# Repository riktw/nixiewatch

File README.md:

# Nixie (ok, panaplex) watch
hardware and software for a panaplex watch.

More info can be found on the corresponding [blog post.](https://justanotherelectronicsblog.com/?p=1190)

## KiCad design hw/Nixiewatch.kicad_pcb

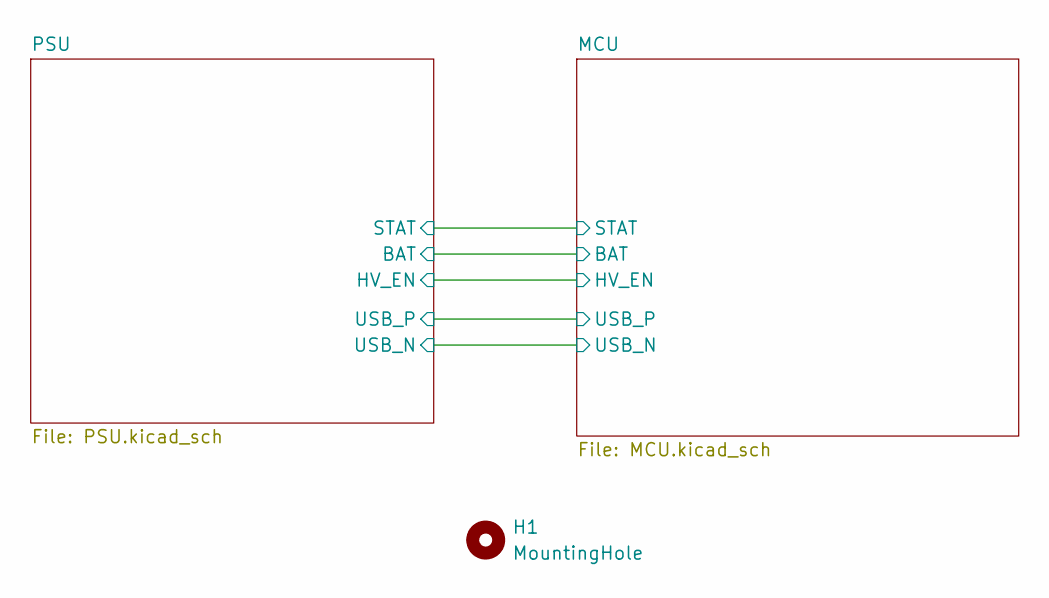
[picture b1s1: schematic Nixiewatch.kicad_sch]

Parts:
H1: MountingHole; MountingHole_2.2mm_M2

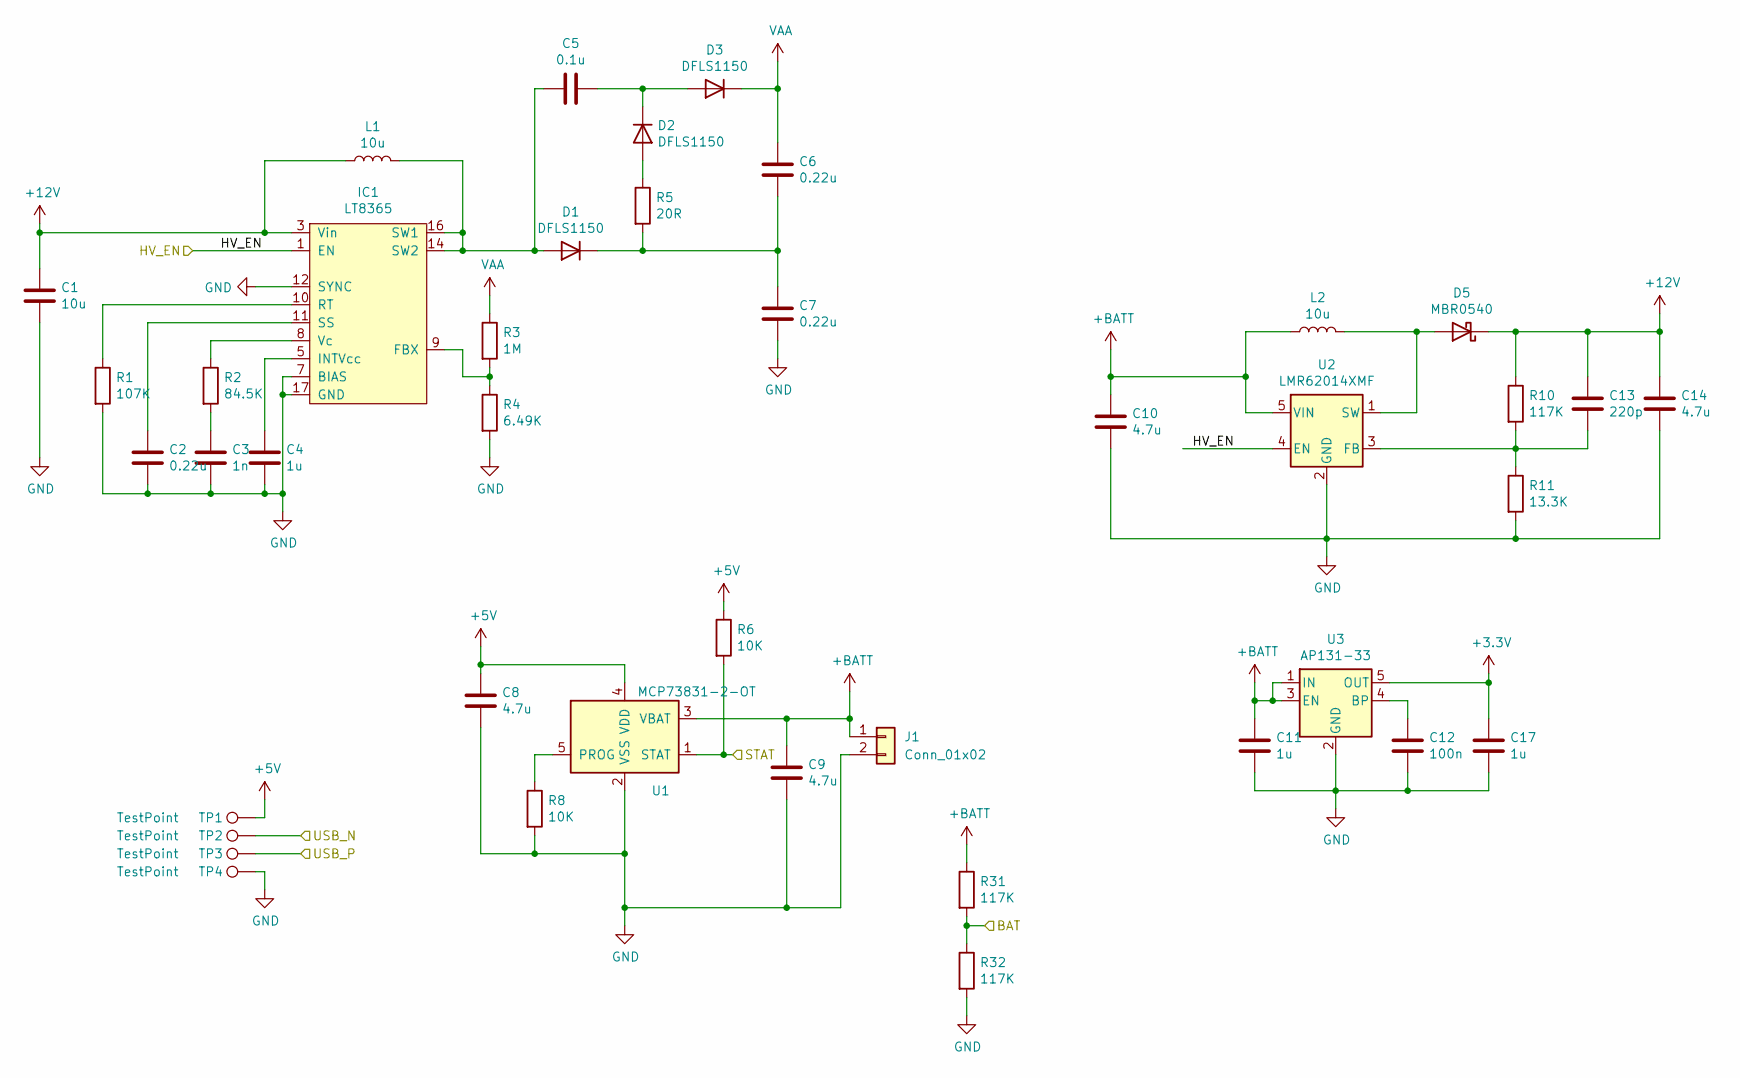
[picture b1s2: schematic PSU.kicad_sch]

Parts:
C1: 10u; C_0805_2012Metric_Pad1.15x1.40mm_HandSolder
C2: 0.22u; C_0603_1608Metric
C3: 1n; C_0603_1608Metric
C4, C11, C17: 1u; C_0603_1608Metric
C5: 0.1u; C_1206_3216Metric
C6, C7: 0.22u; C_1206_3216Metric
C8, C9, C10, C14: 4.7u; C_0603_1608Metric
C12: 100n; C_0603_1608Metric; LCSC C14663
C13: 220p; C_0603_1608Metric
D1, D2, D3: DFLS1150; D_SOD-123
D5: MBR0540; D_SOD-123
IC1: LT8365; MSOP-16-3x4.039_HV
J1: Conn_01x02; PinHeader_1x02_P2.54mm_Vertical
L1, L2: 10u; L_Coilcraft_XxL4020
R1: 107K; R_0603_1608Metric
R2: 84.5K; R_0603_1608Metric
R3: 1M; R_1206_3216Metric
R4: 6.49K; R_0603_1608Metric
R5: 20R; R_0603_1608Metric
R6, R8: 10K; R_0603_1608Metric
R10, R31, R32: 117K; R_0603_1608Metric
R11: 13.3K; R_0603_1608Metric
TP1, TP2, TP3, TP4: TestPoint; TestPoint_Pad_D1.5mm
U1: MCP73831-2-OT; SOT-23-5
U2: LMR62014XMF; SOT-23-5
U3: AP131-33; SOT-23-5

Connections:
+3V3: C17.1, U3.5 (OUT); also elsewhere on the board
+5V: C8.1, R6.1, TP1.1, U1.4 (VDD)
+12V: C1.1, C13.1, C14.1, D5.1 (K), IC1.3 (Vin), L1.1, R10.1
+BATT: C9.1, C10.1, C11.1, J1.1, L2.1, R31.1, U1.3 (VBAT), U2.5 (VIN), U3.1 (IN), U3.3 (EN)
/MCU/BAT: R31.2, R32.1; also elsewhere on the board
/MCU/STAT: R6.2, U1.1 (STAT); also elsewhere on the board
/MCU/USB_N: TP2.1; also elsewhere on the board
/MCU/USB_P: TP3.1; also elsewhere on the board
/PSU/HV_EN: IC1.1 (EN), U2.4 (EN); also elsewhere on the board
GND: C1.2, C2.2, C3.2, C4.2, C7.2, C8.2, C9.2, C10.2, C11.2, C12.2, C14.2, C17.2, IC1.7 (BIAS), IC1.12 (SYNC), IC1.17 (GND), J1.2, R1.2, R4.2, R8.2, R11.2, R32.2, TP4.1, U1.2 (VSS), U2.2 (GND), U3.2 (GND); also elsewhere on the board
unnamed: C2.1, IC1.11 (SS)
unnamed: C3.1, R2.2
unnamed: C4.1, IC1.5 (INTVcc)
unnamed: C5.1, D1.2 (A), IC1.14 (SW2), IC1.16 (SW1), L1.2
unnamed: C5.2, D2.1 (K), D3.2 (A)
unnamed: C6.2, C7.1, D1.1 (K), R5.2
unnamed: C12.1, U3.4 (BP)
unnamed: C13.2, R10.2, R11.1, U2.3 (FB)
unnamed: D2.2 (A), R5.1
unnamed: D5.2 (A), L2.2, U2.1 (SW)
unnamed: IC1.8 (Vc), R2.1
unnamed: IC1.9 (FBX), R3.2, R4.1
unnamed: IC1.10 (RT), R1.1
unnamed: R8.1, U1.5 (PROG)
VAA: C6.1, D3.1 (K), R3.1; also elsewhere on the board

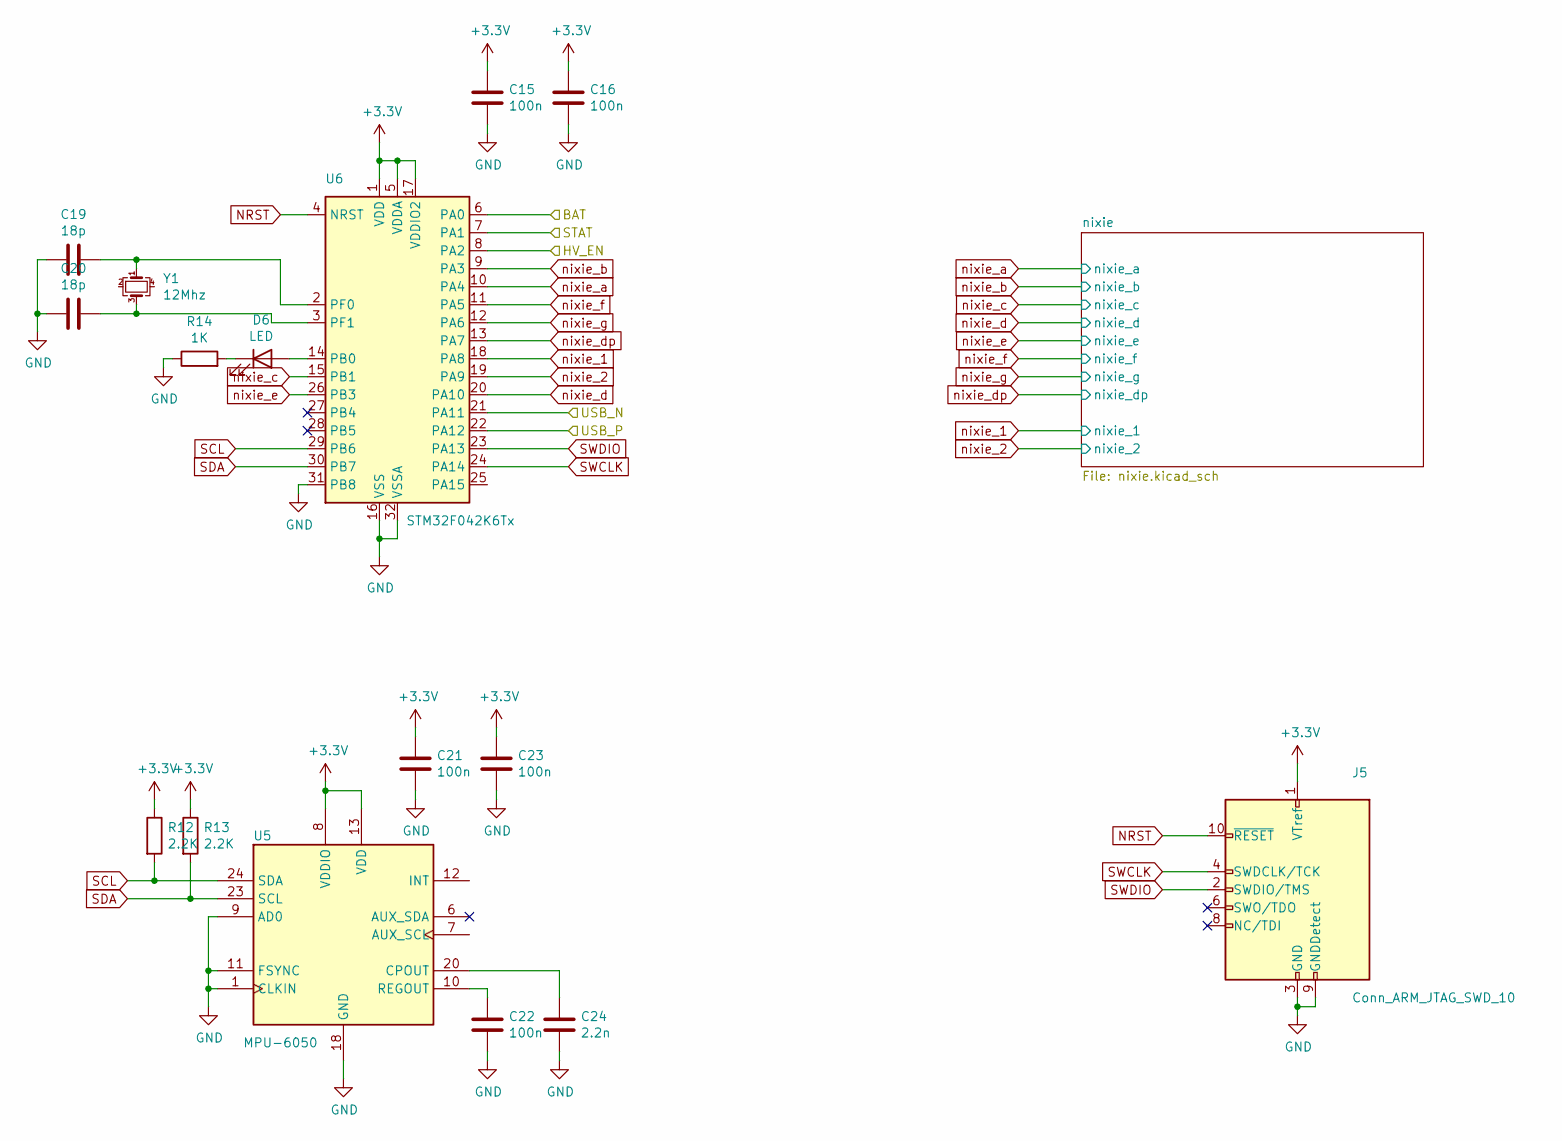
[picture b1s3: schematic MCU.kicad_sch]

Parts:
C15, C16, C21, C22, C23: 100n; C_0603_1608Metric; LCSC C14663
C19, C20: 18p; C_0603_1608Metric
C24: 2.2n; C_0603_1608Metric
D6: LED; LED_0603_1608Metric_Pad1.05x0.95mm_HandSolder
J5: Conn_ARM_JTAG_SWD_10; PinHeader_2x05_P1.27mm_Vertical_SMD
R12, R13: 2.2K; R_0603_1608Metric
R14: 1K; R_0603_1608Metric
U5: MPU-6050; InvenSense_QFN-24_4x4mm_P0.5mm
U6: STM32F042K6Tx; LQFP-32_7x7mm_P0.8mm
Y1: 12Mhz; Crystal_SMD_3225-4Pin_3.2x2.5mm_HandSoldering

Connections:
+3V3: C15.1, C16.1, C21.1, C23.1, J5.1 (VTref), R12.1, R13.1, U5.8 (VDDIO), U5.13 (VDD), U6.1 (VDD), U6.5 (VDDA), U6.17 (VDDIO2); also elsewhere on the board
/MCU/BAT: U6.6 (PA0); also elsewhere on the board
/MCU/STAT: U6.7 (PA1); also elsewhere on the board
/MCU/USB_N: U6.21 (PA11); also elsewhere on the board
/MCU/USB_P: U6.22 (PA12); also elsewhere on the board
/PSU/HV_EN: U6.8 (PA2); also elsewhere on the board
GND: C15.2, C16.2, C19.2, C20.2, C21.2, C22.2, C23.2, C24.2, J5.3 (GND), J5.5 (GND), J5.9 (GNDDetect), R14.1, U5.1 (CLKIN), U5.9 (AD0), U5.11 (FSYNC), U5.18 (GND), U6.16 (VSS), U6.31 (PB8), U6.32 (VSSA); also elsewhere on the board
NRST: J5.10 (~RESET), U6.4 (NRST)
unnamed: C19.1, U6.2 (PF0), Y1.1
unnamed: C20.1, U6.3 (PF1), Y1.3
unnamed: C22.1, U5.10 (REGOUT)
unnamed: C24.1, U5.20 (CPOUT)
unnamed: D6.1 (K), R14.2
unnamed: D6.2 (A), U6.14 (PB0)
SCL: R12.2, U5.24 (SDA), U6.29 (PB6)
SDA: R13.2, U5.23 (SCL), U6.30 (PB7)
SWCLK: J5.4 (SWDCLK/TCK), U6.24 (PA14)
SWDIO: J5.2 (SWDIO/TMS), U6.23 (PA13)
nixie_1: U6.18 (PA8); also elsewhere on the board
nixie_2: U6.19 (PA9); also elsewhere on the board
nixie_a: U6.10 (PA4); also elsewhere on the board
nixie_b: U6.9 (PA3); also elsewhere on the board
nixie_c: U6.15 (PB1); also elsewhere on the board
nixie_d: U6.20 (PA10); also elsewhere on the board
nixie_dp: U6.13 (PA7); also elsewhere on the board
nixie_e: U6.26 (PB3); also elsewhere on the board
nixie_f: U6.11 (PA5); also elsewhere on the board
nixie_g: U6.12 (PA6); also elsewhere on the board

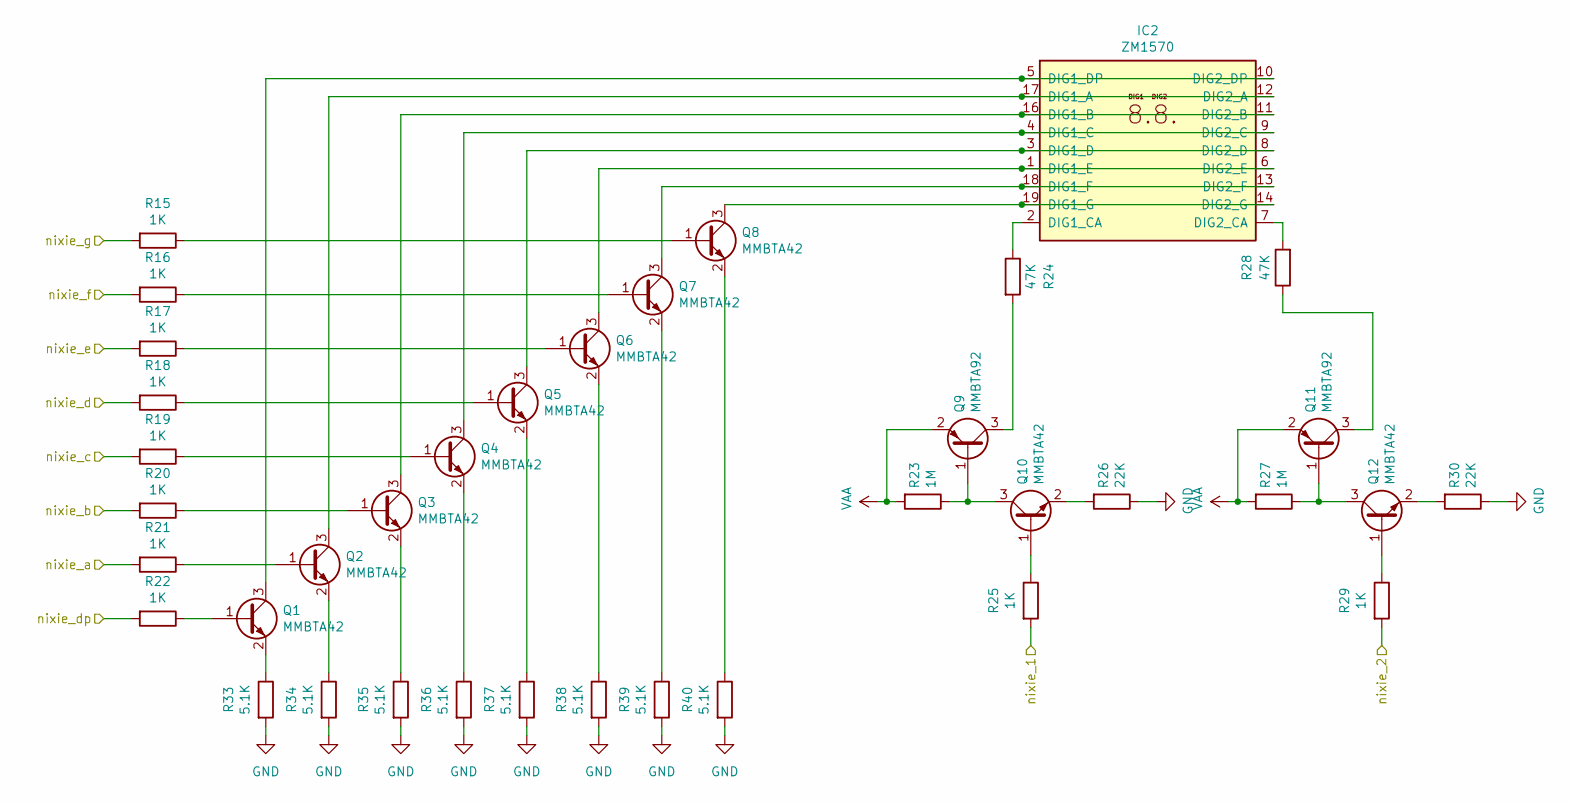
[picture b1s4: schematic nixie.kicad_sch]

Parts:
IC2: ZM1570
Q1, Q2, Q3, Q4, Q5, Q6, Q7, Q8, Q10, Q12: MMBTA42; SOT-23
Q9, Q11: MMBTA92; SOT-23
R15, R16, R17, R18, R19, R20, R21, R22, R25, R29: 1K; R_0603_1608Metric
R23, R27: 1M; R_0603_1608Metric
R24, R28: 47K; R_0805_2012Metric_Pad1.15x1.40mm_HandSolder
R26, R30: 22K; R_0603_1608Metric
R33, R34, R35, R36, R37, R38, R39, R40: 5.1K; R_0603_1608Metric

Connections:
GND: R26.1, R30.1, R33.2, R34.2, R35.2, R36.2, R37.2, R38.2, R39.2, R40.2; also elsewhere on the board
unnamed: IC2.1 (DIG1_E), IC2.6 (DIG2_E), Q6.3 (C)
unnamed: IC2.2 (DIG1_CA), R24.1
unnamed: IC2.3 (DIG1_D), IC2.8 (DIG2_D), Q5.3 (C)
unnamed: IC2.4 (DIG1_C), IC2.9 (DIG2_C), Q4.3 (C)
unnamed: IC2.7 (DIG2_CA), R28.2
unnamed: IC2.5 (DIG1_DP), IC2.10 (DIG2_DP), Q1.3 (C)
unnamed: IC2.11 (DIG2_B), IC2.16 (DIG1_B), Q3.3 (C)
unnamed: IC2.12 (DIG2_A), IC2.17 (DIG1_A), Q2.3 (C)
unnamed: IC2.13 (DIG2_F), IC2.18 (DIG1_F), Q7.3 (C)
unnamed: IC2.14 (DIG2_G), IC2.19 (DIG1_G), Q8.3 (C)
unnamed: Q1.1 (B), R22.1
unnamed: Q1.2 (E), R33.1
unnamed: Q2.1 (B), R21.1
unnamed: Q2.2 (E), R34.1
unnamed: Q3.1 (B), R20.1
unnamed: Q3.2 (E), R35.1
unnamed: Q4.1 (B), R19.1
unnamed: Q4.2 (E), R36.1
unnamed: Q5.1 (B), R18.1
unnamed: Q5.2 (E), R37.1
unnamed: Q6.1 (B), R17.1
unnamed: Q6.2 (E), R38.1
unnamed: Q7.1 (B), R16.1
unnamed: Q7.2 (E), R39.1
unnamed: Q8.1 (B), R15.1
unnamed: Q8.2 (E), R40.1
unnamed: Q9.3 (C), R24.2
unnamed: Q10.1 (B), R25.1
unnamed: Q10.2 (E), R26.2
unnamed: Q9.1 (B), Q10.3 (C), R23.1
unnamed: Q11.1 (B), Q12.3 (C), R27.1
unnamed: Q11.3 (C), R28.1
unnamed: Q12.1 (B), R29.1
unnamed: Q12.2 (E), R30.2
VAA: Q9.2 (E), Q11.2 (E), R23.2, R27.2; also elsewhere on the board
nixie_1: R25.2; also elsewhere on the board
nixie_2: R29.2; also elsewhere on the board
nixie_a: R21.2; also elsewhere on the board
nixie_b: R20.2; also elsewhere on the board
nixie_c: R19.2; also elsewhere on the board
nixie_d: R18.2; also elsewhere on the board
nixie_dp: R22.2; also elsewhere on the board
nixie_e: R17.2; also elsewhere on the board
nixie_f: R16.2; also elsewhere on the board
nixie_g: R15.2; also elsewhere on the board

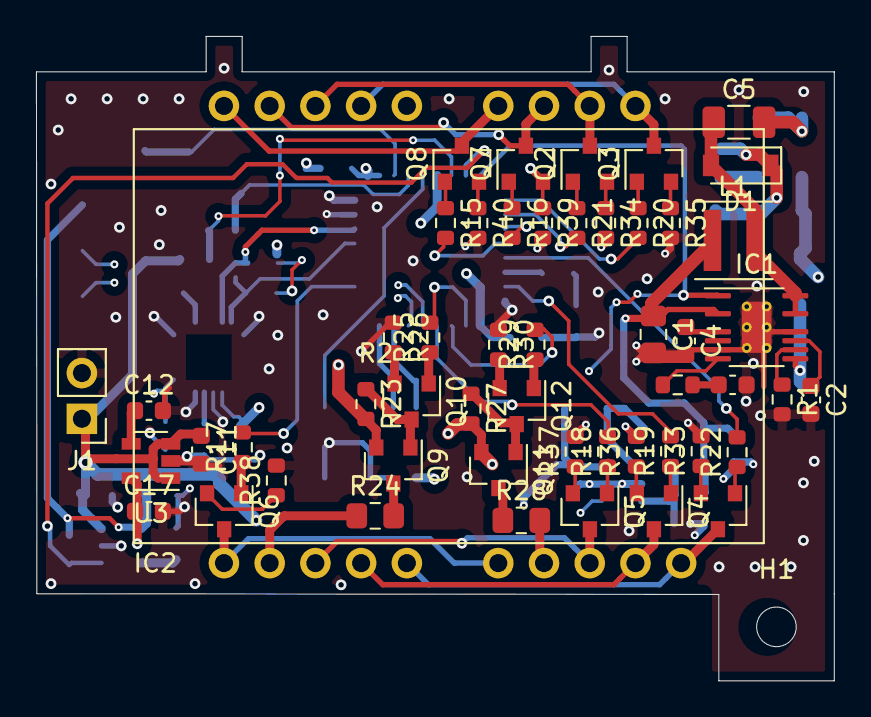
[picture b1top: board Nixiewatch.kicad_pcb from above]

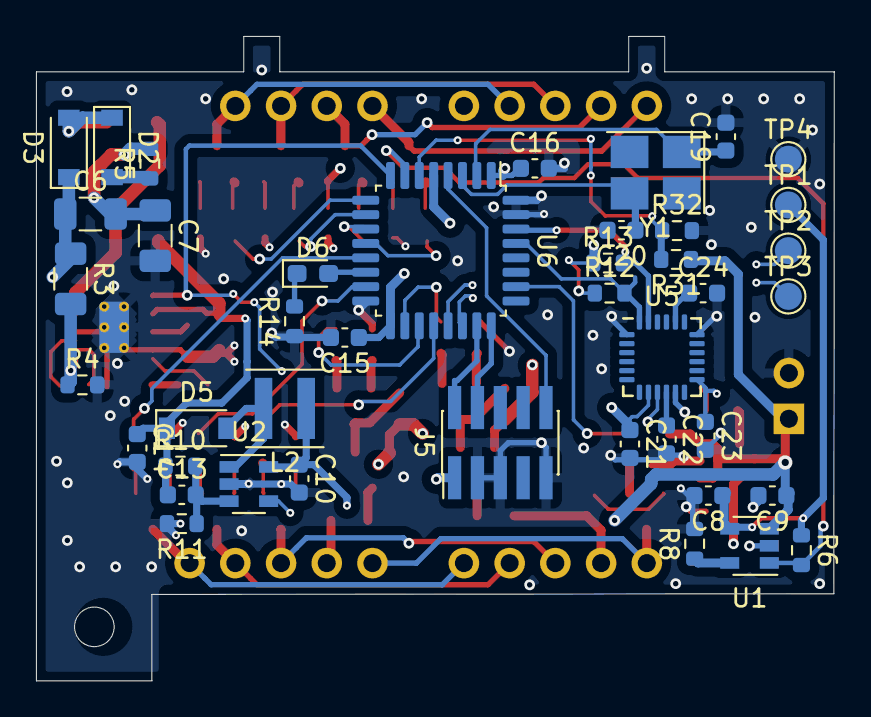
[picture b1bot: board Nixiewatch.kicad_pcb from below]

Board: 4 copper layers, 44.3 x 35.8 mm, 95 parts (42 on the bottom side), 80 nets.

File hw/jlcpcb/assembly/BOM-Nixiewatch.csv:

Comment,Designator,Footprint,LCSC
100n,"C15,C16,C21,C22,C23",C_0603_1608Metric,C14663
MCP73831-2-OT,U1,SOT-23-5,C14879
220p,C13,C_0603_1608Metric,C1603
2.2n,C24,C_0603_1608Metric,C1604
18p,"C19,C20",C_0603_1608Metric,C1647
4.7u,"C10,C14,C9",C_0603_1608Metric,C19666
1K,R14,R_0603_1608Metric,C21190
MPU-6050,U5,InvenSense_QFN-24_4x4mm_P0.5mm,C24112
10K,"R6,R8",R_0603_1608Metric,C25804
2.2K,"R12,R13",R_0603_1608Metric,C4190
STM32F042K6Tx,U6,LQFP-32_7x7mm_P0.8mm,C69216
12Mhz,Y1,Crystal_SMD_3225-4Pin_3.2x2.5mm_HandSoldering,C9002
ZM1570,IC2,ZM1570,
TestPoint,TP4,TestPoint_Pad_D1.5mm,
TestPoint,TP3,TestPoint_Pad_D1.5mm,
TestPoint,TP2,TestPoint_Pad_D1.5mm,
TestPoint,TP1,TestPoint_Pad_D1.5mm,
Conn_01x02,J1,PinHeader_1x02_P2.54mm_Vertical,
MountingHole,H1,MountingHole_2.2mm_M2,
1u,C11,C_0603_1608Metric,
100n,C12,C_0603_1608Metric,
1K,R20,R_0603_1608Metric,
MMBTA92,Q11,SOT-23,
MMBTA42,Q7,SOT-23,
MMBTA92,Q9,SOT-23,
1K,R19,R_0603_1608Metric,
1K,R18,R_0603_1608Metric,
1K,R17,R_0603_1608Metric,
MMBTA42,Q8,SOT-23,
MMBTA42,Q5,SOT-23,
MMBTA42,Q2,SOT-23,
1K,R25,R_0603_1608Metric,
47K,R24,R_0805_2012Metric_Pad1.15x1.40mm_HandSolder,
1u,C17,C_0603_1608Metric,
MMBTA42,Q1,SOT-23,
MMBTA42,Q6,SOT-23,
MMBTA42,Q10,SOT-23,
MMBTA42,Q4,SOT-23,
MMBTA42,Q12,SOT-23,
1M,R27,R_0603_1608Metric,
22K,R26,R_0603_1608Metric,
1M,R23,R_0603_1608Metric,
1K,R22,R_0603_1608Metric,
1K,R16,R_0603_1608Metric,
1K,R15,R_0603_1608Metric,
AP131-33,U3,SOT-23-5,
22K,R30,R_0603_1608Metric,
MMBTA42,Q3,SOT-23,
1K,R29,R_0603_1608Metric,
47K,R28,R_0805_2012Metric_Pad1.15x1.40mm_HandSolder,
1K,R21,R_0603_1608Metric,
107K,R1,R_0603_1608Metric,
84.5K,R2,R_0603_1608Metric,
10u,C1,C_0805_2012Metric_Pad1.15x1.40mm_HandSolder,
1n,C3,C_0603_1608Metric,
1u,C4,C_0603_1608Metric,
LT8365,IC1,MSOP-16-3x4.039_HV,
10u,L1,L_Coilcraft_XxL4020,
0.22u,C2,C_0603_1608Metric,
0.1u,C5,C_1206_3216Metric,
5.1K,R36,R_0603_1608Metric,
5.1K,R37,R_0603_1608Metric,
10K,R33,R_0603_1608Metric,
5.1K,R35,R_0603_1608Metric,
5.1K,R39,R_0603_1608Metric,
DFLS1150,D1,D_SOD-123,
5.1K,R34,R_0603_1608Metric,
5.1K,R40,R_0603_1608Metric,
5.1K,R38,R_0603_1608Metric,
MBR0540,D5,D_SOD-123,
10u,L2,L_Coilcraft_XxL4020,
117K,R10,R_0603_1608Metric,
13.3K,R11,R_0603_1608Metric,
LMR62014XMF,U2,SOT-23-5,
Conn_ARM_JTAG_SWD_10,J5,PinHeader_2x05_P1.27mm_Vertical_SMD,
LED,D6,LED_0603_1608Metric_Pad1.05x0.95mm_HandSolder,
DFLS1150,D2,D_SOD-123,
DFLS1150,D3,D_SOD-123,
0.22u,C6,C_1206_3216Metric,
0.22u,C7,C_1206_3216Metric,
6.49K,R4,R_0603_1608Metric,
20R,R5,R_0603_1608Metric,
1M,R3,R_1206_3216Metric,
117K,R31,R_0603_1608Metric,
117K,R32,R_0603_1608Metric,

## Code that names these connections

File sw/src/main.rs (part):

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
static USB_SERIAL: Mutex<RefCell<Option<UsbSerial>>> = Mutex::new(RefCell::new(None));

static CHARGE_STATUS: Mutex<RefCell<Option<gpioa::PA1<Input<Floating>>>>> = Mutex::new(RefCell::new(None));

static BATTERY_VOLTAGE: Mutex<RefCell<Option<gpioa::PA0<Analog>>>> = Mutex::new(RefCell::new(None));
static ADC: Mutex<RefCell<Option<Adc<>>>> = Mutex::new(RefCell::new(None));

static MPU: Mutex<RefCell<Option<mpu6050::Mpu6050<I2c<I2C1,
gpiob::PB6<Alternate<AF1>>,
gpiob::PB7<Alternate<AF1>>>>
>>> = Mutex::new(RefCell::new(None));

// Make external interrupt registers globally available
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fn EXTI4_15() {
  static mut EXINT: Option<EXTI> = None;
  static mut XMPU: Option<mpu6050::Mpu6050<I2c<I2C1,
  gpiob::PB6<Alternate<AF1>>,
  gpiob::PB7<Alternate<AF1>>>>> = None;

  let exti = EXINT.get_or_insert_with(|| {
    cortex_m::interrupt::free(|cs| {
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fn TIM14() {
  static mut INT: Option<Timer<TIM14>> = None;
  static mut NIXIEDISPLAY: Option<NixieClock> = None;
  static mut CHARGESTATUS: Option<gpioa::PA1<Input<Floating>>> = None;
  static mut COUNTER: u8 = 0;

  static mut BATTERYVOLTAGE: Option<gpioa::PA0<Analog>> = None;
  static mut SADC: Option<Adc<>> = None;

  let int = INT.get_or_insert_with(|| {
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      exti.imr.modify(|_, w| w.mr4().set_bit());
      exti.rtsr.modify(|_, w| w.tr4().set_bit());

      let mut nixie1 = gpioa.pa8.into_push_pull_output(cs);
      let mut nixie2 = gpioa.pa9.into_push_pull_output(cs);

      let nixie_a = gpioa.pa4.into_push_pull_output(cs);
      let nixie_b = gpioa.pa3.into_push_pull_output(cs);
      let nixie_c = gpiob.pb1.into_push_pull_output(cs);
      let nixie_d = gpioa.pa10.into_push_pull_output(cs);
      let nixie_e = gpiob.pb3.into_push_pull_output(cs);
      let nixie_f = gpioa.pa5.into_push_pull_output(cs);
      let nixie_g = gpioa.pa6.into_push_pull_output(cs);
      let mut nixie_dp = gpioa.pa7.into_push_pull_output(cs);
      
      let mut hv_enable = gpioa.pa2.into_push_pull_output(cs);

      let charge_status = gpioa.pa1.into_floating_input(cs);

      //initial states
      nixie_dp.set_low().ok();
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      *NIXIE_DISPLAY.borrow(cs).borrow_mut() = Some(nixie_clock);

      //setup i2c for the gyro
      let sda = gpiob.pb7.into_alternate_af1(cs);
      let scl = gpiob.pb6.into_alternate_af1(cs);

      let i2c = I2c::i2c1(p.I2C1, (scl, sda), 100.khz(), &mut rcc);
      let mut mpu = Mpu6050::new(i2c);
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
      // Init the ADC
      let adc = Adc::new(p.ADC, &mut rcc);
      let battery_voltage = gpioa.pa0.into_analog(cs);
      *ADC.borrow(cs).borrow_mut() = Some(adc);
      *BATTERY_VOLTAGE.borrow(cs).borrow_mut() = Some(battery_voltage);

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
      let usb = Peripheral {
        usb: p.USB,
        pin_dm: gpioa.pa11,
        pin_dp: gpioa.pa12,
      };

      let mut usb_serial = UsbSerial::new();
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
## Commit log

2022-10-25 Initial commit of this ugly mess
2022-12-20 Added latest nixie watch sw, moved to sw folder
2022-12-20 Added hardware design files as well
2022-12-20 Added license
2022-12-20 Oops .cargo also needs to be in sw folder
